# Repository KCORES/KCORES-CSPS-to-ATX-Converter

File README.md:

# KCORES-CSPS-to-ATX-Converter

- 项目视频: [1元10瓦 垃圾佬的超级ATX电源-Youtube](https://www.youtube.com/watch?v=Dy0Jgn7Dg4A)
- KCORES 交流群: [826702309](https://jq.qq.com/?_wv=1027&k=jcr07ZYG)
- KCORES 官方网站: [KCORES.com](https://kcores.com/)
- 从零开始制作: [入门指南](Document/Getting_Started_Guide.md)

# Specification

| 12V   | 5V    | 3.3V  | 5VSB  |
|-------|-------|-------|-------|
|取决于CSPS| 5A | 5A    | 5A    |
|       | 25W   | 16.5W | 25W   |

⚠: 5V 与 3.3V 不建议长期超过 4A 使用

## 模组接口
- 1x 24Pin 主板接口 (巨龙线序)
- 1x 4Pin IDE/SATA 硬盘接口 (联想线序)
- 5x 8Pin CPU/GPU 接口 (巨龙线序)
- 1x I2C PMBUS 控制接口

# Document

## Distinguish CSPS

KCORES CSPS to ATX Converter 可以用于引脚特征如下图所示的电源

目前已知 Hewlett Packard Enterprise 与 Huawei 大量生产过 CSPS.  
不同厂家生产的 CSPS 可能外形略有不同, 但金手指必须与图示一致才可使用.  

## Getting Started Guide

- [入门指南](Document/Getting_Started_Guide.md)

# LICENSE

# Contributor

- [@AlphaArea](https://github.com/alphaarea)
- @Ubiq
- [@karminski-牙医](https://github.com/karminski)
- [@MistyMoonR](https://github.com/MistyMoonR)

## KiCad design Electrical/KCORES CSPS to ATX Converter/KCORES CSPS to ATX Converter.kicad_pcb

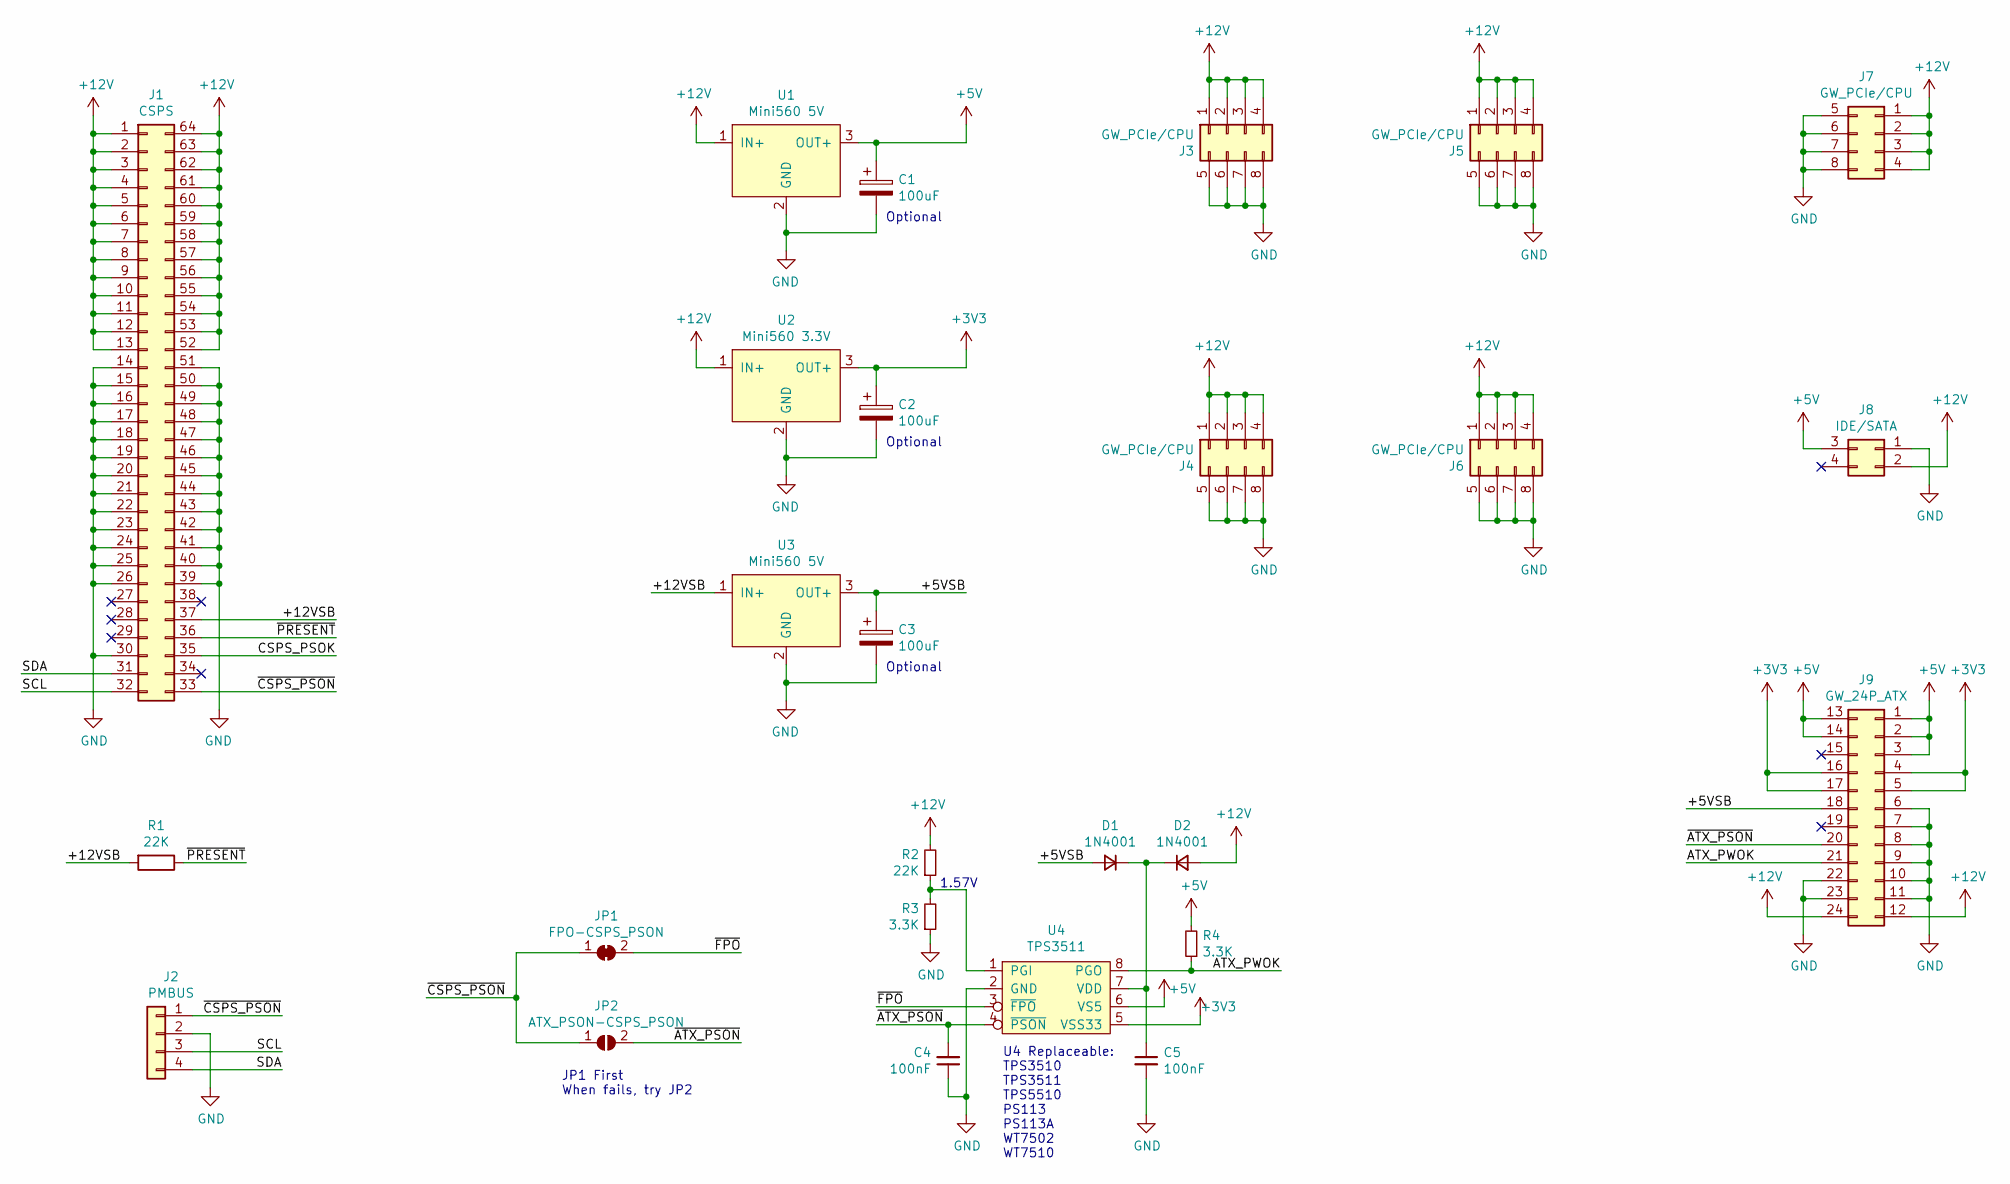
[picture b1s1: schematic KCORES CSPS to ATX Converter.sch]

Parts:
C1, C2, C3: 100uF; CP_EIA-7343-31_Kemet-D_Pad2.25x2.55mm_HandSolder
C4, C5: 100nF; C_Disc_D5.0mm_W2.5mm_P2.50mm
D1, D2: 1N4001; D_DO-41_SOD81_P7.62mm_Horizontal
J1: CSPS; CSPS_64P_2.54mm
J2: PMBUS; PinHeader_1x04_P2.54mm_Vertical
J3, J4, J5, J6, J7: GW_PCIe/CPU; ATX_8Pin_P4.20mm_Vertical_4.20mm
J8: IDE/SATA; ATX_4Pin_P4.20mm_Vertical_4.20mm
J9: GW_24P_ATX; ATX_24Pin_P4.20mm_Vertical_4.20mm
JP1: FPO-CSPS_PSON; SolderJumper-2_P1.3mm_Bridged_RoundedPad1.0x1.5mm
JP2: ATX_PSON-CSPS_PSON; SolderJumper-2_P1.3mm_Open_RoundedPad1.0x1.5mm
R1, R2: 22K; R_Axial_DIN0207_L6.3mm_D2.5mm_P7.62mm_Horizontal
R3, R4: 3.3K; R_Axial_DIN0207_L6.3mm_D2.5mm_P7.62mm_Horizontal
U1, U3: Mini560 5V; Converter_DCDC_Mini_560
U2: Mini560 3.3V; Converter_DCDC_Mini_560
U4: TPS3511; DIP-8_W7.62mm

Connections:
+3V3: C2.1, J9.4, J9.5, J9.16, J9.17, U2.3 (OUT+), U4.5 (VSS33)
+5V: C1.1, J8.3, J9.1, J9.2, J9.3, J9.13, J9.14, R4.2, U1.3 (OUT+), U4.6 (VS5)
+12V: D2.2 (A), J1.1, J1.2, J1.3, J1.4, J1.5, J1.6, J1.7, J1.8, J1.9, J1.10, J1.11, J1.12, J1.13, J1.52, J1.53, J1.54, J1.55, J1.56, J1.57, J1.58, J1.59, J1.60, J1.61, J1.62, J1.63, J1.64, J3.1, J3.2, J3.3, J3.4, J4.1, J4.2, J4.3, J4.4, J5.1, J5.2, J5.3, J5.4, J6.1, J6.2, J6.3, J6.4, J7.1, J7.2, J7.3, J7.4, J8.2, J9.12, J9.24, R2.2, U1.1 (IN+), U2.1 (IN+)
/+5VSB: C3.1, D1.2 (A), J9.18, U3.3 (OUT+)
/+12VSB: J1.37, R1.2, U3.1 (IN+)
/ATX_PWOK: J9.21, R4.1, U4.8 (PGO)
/CSPS_PSOK: J1.35
/SCL: J1.32, J2.3
/SDA: J1.31, J2.4
/~ATX_PSON: C4.2, J9.20, JP2.2 (B), U4.4 (~PSON)
/~CSPS_PSON: J1.33, J2.1, JP1.1 (A), JP2.1 (A)
/~FPO: JP1.2 (B), U4.3 (~FPO)
/~PRESENT: J1.36, R1.1
GND: C1.2, C2.2, C3.2, C4.1, C5.2, J1.14, J1.15, J1.16, J1.17, J1.18, J1.19, J1.20, J1.21, J1.22, J1.23, J1.24, J1.25, J1.26, J1.30, J1.39, J1.40, J1.41, J1.42, J1.43, J1.44, J1.45, J1.46, J1.47, J1.48, J1.49, J1.50, J1.51, J2.2, J3.5, J3.6, J3.7, J3.8, J4.5, J4.6, J4.7, J4.8, J5.5, J5.6, J5.7, J5.8, J6.5, J6.6, J6.7, J6.8, J7.5, J7.6, J7.7, J7.8, J8.1, J9.6, J9.7, J9.8, J9.9, J9.10, J9.11, J9.22, J9.23, R3.1, U1.2 (GND), U2.2 (GND), U3.2 (GND), U4.2 (GND)
unnamed: C5.1, D1.1 (K), D2.1 (K), U4.7 (VDD)
unnamed: R2.1, R3.2, U4.1 (PGI)

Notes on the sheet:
Optional
1.57V
JP1 First When fails, try JP2
U4 Replaceable: TPS3510 TPS3511 TPS5510 PS113 PS113A WT7502 WT7510

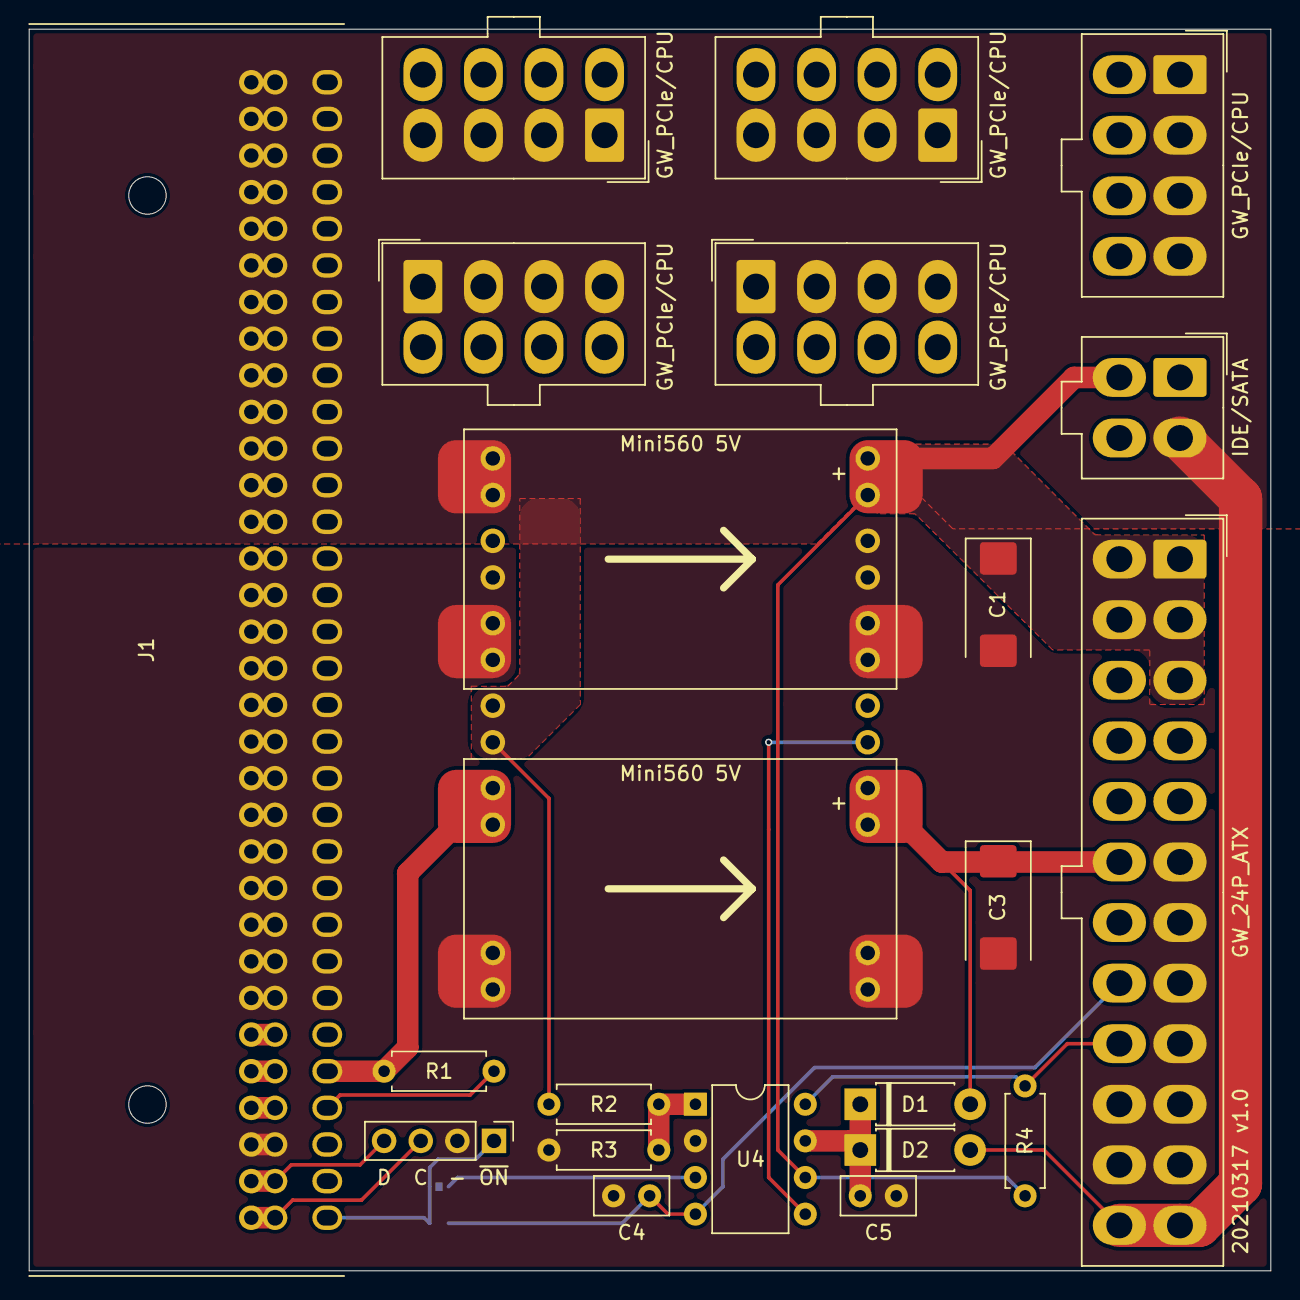
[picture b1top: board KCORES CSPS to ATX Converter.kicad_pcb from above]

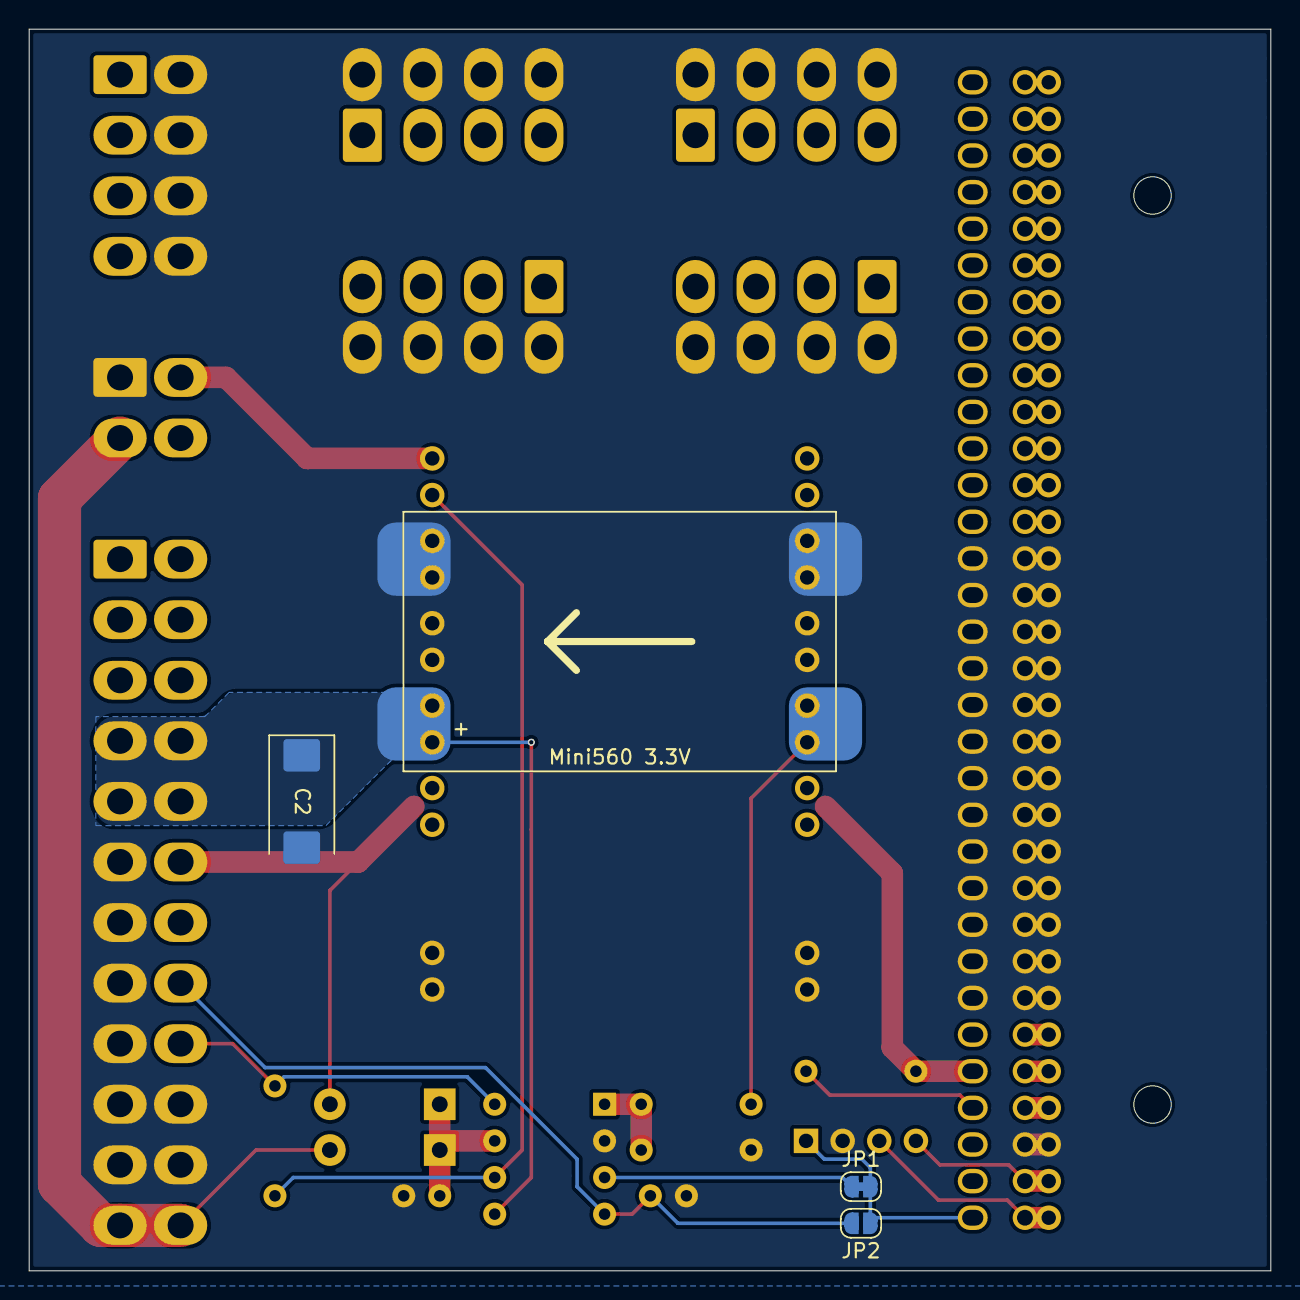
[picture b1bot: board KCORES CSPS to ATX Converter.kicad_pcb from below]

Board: 2 copper layers, 86.1 x 86.1 mm, 26 parts (4 on the bottom side), 15 nets.

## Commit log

2021-03-31 v1.0
2021-04-04 Update Guide
2021-04-04 update Arduino lib
2021-09-08 feat: pmbus read checksum fix, add esphome example
2021-09-08 docs(esphome): update sensors example
2021-09-16 fix: Serial.printf not exist on some environment
2021-09-17 feat: need CSPS_ERROR_TO_SERIAL define to use serial
2021-09-17 feat: impl retry
2022-06-02 fix: rename esphome main.cpp to main.hpp
2022-06-02 docs(esphome): update ESPHome example

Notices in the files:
Electrical/KCORES CSPS to ATX Converter/KCORES CSPS to ATX Converter.kicad_pcb:
License: KCORES Open Source License
